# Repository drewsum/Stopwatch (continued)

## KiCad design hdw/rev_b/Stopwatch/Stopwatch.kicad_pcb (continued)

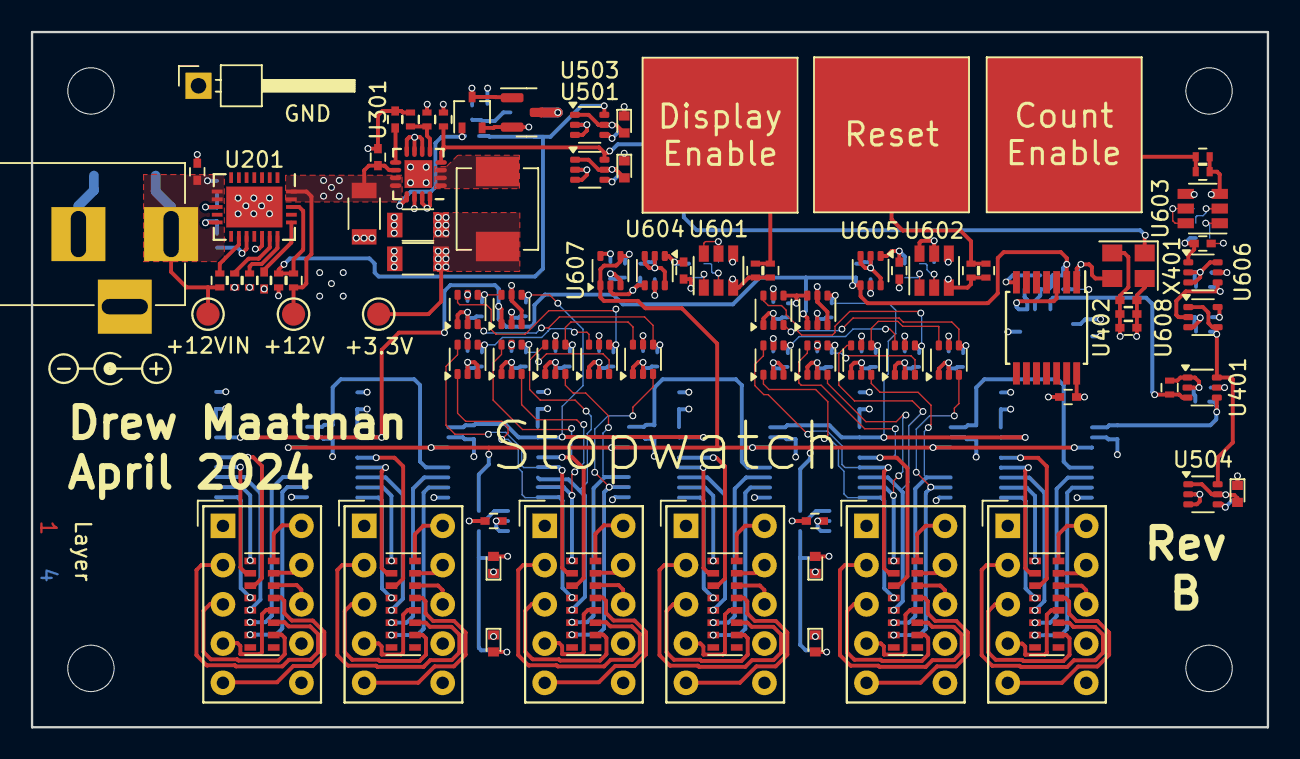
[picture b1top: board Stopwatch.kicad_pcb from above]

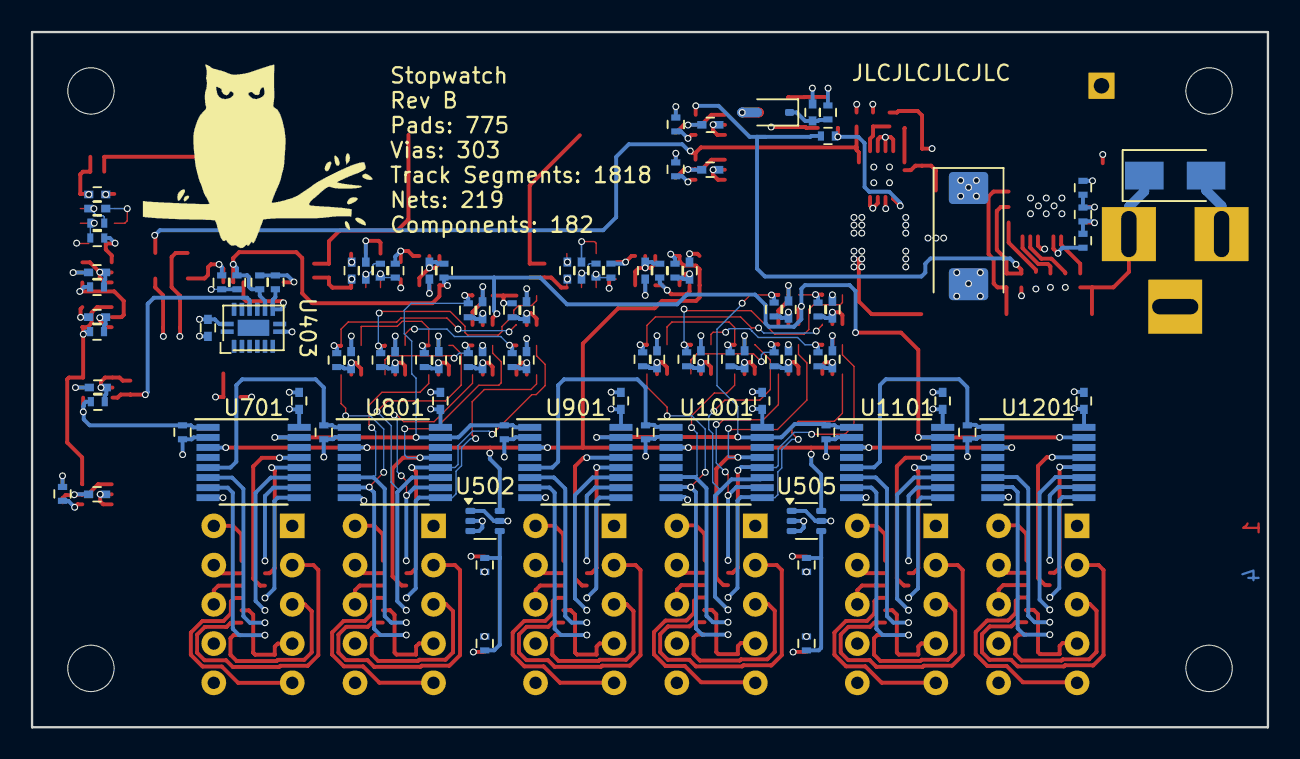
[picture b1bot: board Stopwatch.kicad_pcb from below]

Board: 4 copper layers, 80.0 x 45.0 mm, 192 parts (97 on the bottom side), 156 nets.

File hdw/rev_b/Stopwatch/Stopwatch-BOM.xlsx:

Reference | Value | Datasheet | Footprint | Qty | DNP | Config | Digi-Key PN
C201,C303,C402,C601,C602,C603 | 10nF |  | Capacitors_SMD:C_0402 | 6 |  |  | 445-12201-1-ND
C202,C304,C401,C404,C405,C406,C501,C502,C503,C504,C505,C604,C605,C606,C610,C611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 | 0.1uF |  | Capacitors_SMD:C_0402 | 39 |  |  | 490-10697-1-ND
C203 | 100uF |  | Capacitor_Tantalum_SMD:CP_EIA-7343-43_Kemet-X | 1 |  |  | 718-1102-1-ND
C301,C305,C306 | 10uF |  | Capacitors_SMD:C_1206 | 3 |  |  | 1276-7031-1-ND
C302,C607,C608,C609 | 10uF |  | Capacitors_SMD:C_0402 | 4 |  |  | 490-GRM155R61A106ME11DCT-ND
C403 | 1nF |  | Capacitors_SMD:C_0402 | 1 |  |  | 445-7376-1-ND
D201 | 24V | ~ | Diodes_SMD:D_SMA | 1 | DNP | DNP | SMAJ24CALFCT-ND
D301 | BAT48JFILM | www.st.com/resource/en/datasheet/bat48.pdf | Diode_SMD:D_SOD-323 | 1 |  |  | 497-5711-1-ND
D501,D504,D505 | Green | ~ | LEDs:LED_0402 | 3 |  |  | 754-1101-1-ND
D502,D503,D506,D507 | Red | ~ | LEDs:LED_0402 | 4 |  |  | 754-1104-1-ND
H1501,H1502,H1503,H1504 | 3mm | ~ | MountingHole:MountingHole_3mm | 4
J201 | +12V IN | ~ | Connectors:BARREL_JACK | 1 |  |  | CP-202BH-ND
L301 | 2.2u |  | Inductors_SMD:L_Vishay_IHLP-2020 | 1 |  |  | 541-1236-1-ND
N201 | +12V 1A Power Supply | ~ |  | 1 |  |  | 993-1335-ND
Q301 | BSS214NW | https://www.infineon.com/dgdl/Infineon-BSS214NW-DS-v02_02-en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 | Package_TO_SOT_SMD:SOT-323_SC-70 | 1 |  |  | BSS214NWH6327XTSA1CT-ND
Q302 | ZXMS6004FFTA | https://www.diodes.com/assets/Datasheets/ZXMS6004FF.pdf | Package_TO_SOT_SMD:SOT-23 | 1 |  |  | ZXMS6004FFCT-ND
R201 | 51.1k |  | Resistors_SMD:R_0402 | 1 |  |  | RMCF0402FT51K1CT-ND
R202 | 1.15k |  | Resistors_SMD:R_0402 | 1 |  |  | RMCF0402FT1K15CT-ND
R203,R207 | 5.11k |  | Resistors_SMD:R_0402 | 2 |  |  | RMCF0402FT5K11CT-ND
R204,R205,R208,R302,R303,R401,R402,R403,R404,R405,R406,R607,R608,R609,R610,R611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 | 10k |  | Resistors_SMD:R_0402 | 42 |  |  | RMCF0402FT10K0CT-ND
R206 | 13k |  | Resistors_SMD:R_0402 | 1 |  |  | RMCF0402FT13K0CT-ND
R301 | 10 |  | Resistors_SMD:R_0402 | 1 |  |  | RMCF0402FT10R0CT-ND
R304 | 562k |  | Resistors_SMD:R_0402 | 1 |  |  | RMCF0402FT562KCT-ND
R305 | 180k |  | Resistors_SMD:R_0402 | 1 |  |  | RMCF0402FT180KCT-ND
R501,R502,R503,R504,R505,R506,R507,R601,R602,R603,R604,R605,R606 | 1k |  | Resistors_SMD:R_0402 | 13 |  |  | RMCF0402FT1K00CT-ND
RN701,RN801,RN901,RN1001,RN1101,RN1201 | 1k |  | Resistor_SMD:R_Cat16-8 | 6 |  |  | CAT16-102J8LFCT-ND
SW601,SW602,SW603 | Cap_Touch |  | Custom Footprints Library:Capacitive_Touch_Pad | 3
TP201 | TP |  | Connector_PinHeader_2.54mm:PinHeader_1x01_P2.54mm_Horizontal | 1
TP202,TP203 | TP_Pad |  | Custom Footprints Library:Test_Point | 2
TP301 | TP |  | Custom Footprints Library:Test_Point | 1
U201 | TPS26600RHFT | http://www.ti.com/lit/ds/symlink/tps2660.pdf | Housings_DFN_QFN:QFN-24-1EP_4x5mm_Pitch0.5mm | 1 |  |  | 296-45478-1-ND
U301 | TPS62130A | http://www.ti.com/lit/ds/symlink/tps62130.pdf | Housings_DFN_QFN:QFN-16-1EP_3x3mm_Pitch0.5mm | 1 |  |  | 296-39446-1-ND
U401,U501,U502,U503,U504,U505,U604,U605,U606,U1301,U1302,U1303,U1304,U1305,U130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 | 74LVC1G97 | http://www.ti.com/lit/ds/symlink/sn74lvc1g97.pdf | Package_TO_SOT_SMD:SOT-363_SC-70-6 | 23 |  |  | 296-15582-1-ND
U402 | CD4024 | http://www.ti.com/lit/ds/symlink/cd4020b.pdf | Housings_SSOP:TSSOP-14_4.4x5mm_Pitch0.65mm | 1 |  |  | 296-49578-ND
U403 | CD4040 | http://www.intersil.com/content/dam/Intersil/documents/cd40/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 | Custom Footprints Library:DHVQFN16-1ep_3p5x2p5mm | 1 |  |  | 1727-7992-1-ND
U601,U602,U603 | AT42QT1010-TSHR | http://ww1.microchip.com/downloads/en/DeviceDoc/Atmel-9541-A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 | TO_SOT_Packages_SMD:SOT-23-6 | 3 |  |  | AT42QT1010-TSHRCT-ND
U607,U608 | 74LVC1G80 | http://www.ti.com/lit/sg/scyt129e/scyt129e.pdf | Package_TO_SOT_SMD:SOT-353_SC-70-5 | 2 |  |  | 296-41824-1-ND
U701,U801,U901,U1001,U1101,U1201 | 4026 |  | Housings_SSOP:TSSOP-16_4.4x5mm_Pitch0.65mm | 6 |  |  | 296-32878-5-ND
U702,U802,U902,U1002,U1102,U1202 | HDSP-7503 | https://docs.broadcom.com/docs/AV02-2553EN | Display_7Segment:HDSP-A151 | 6 |  |  | 516-1203-5-ND
X401 | ECS-327KE |  | Oscillator:Oscillator_SMD_Abracon_ASE-4Pin_3.2x2.5mm | 1 |  |  | XC1751CT-ND

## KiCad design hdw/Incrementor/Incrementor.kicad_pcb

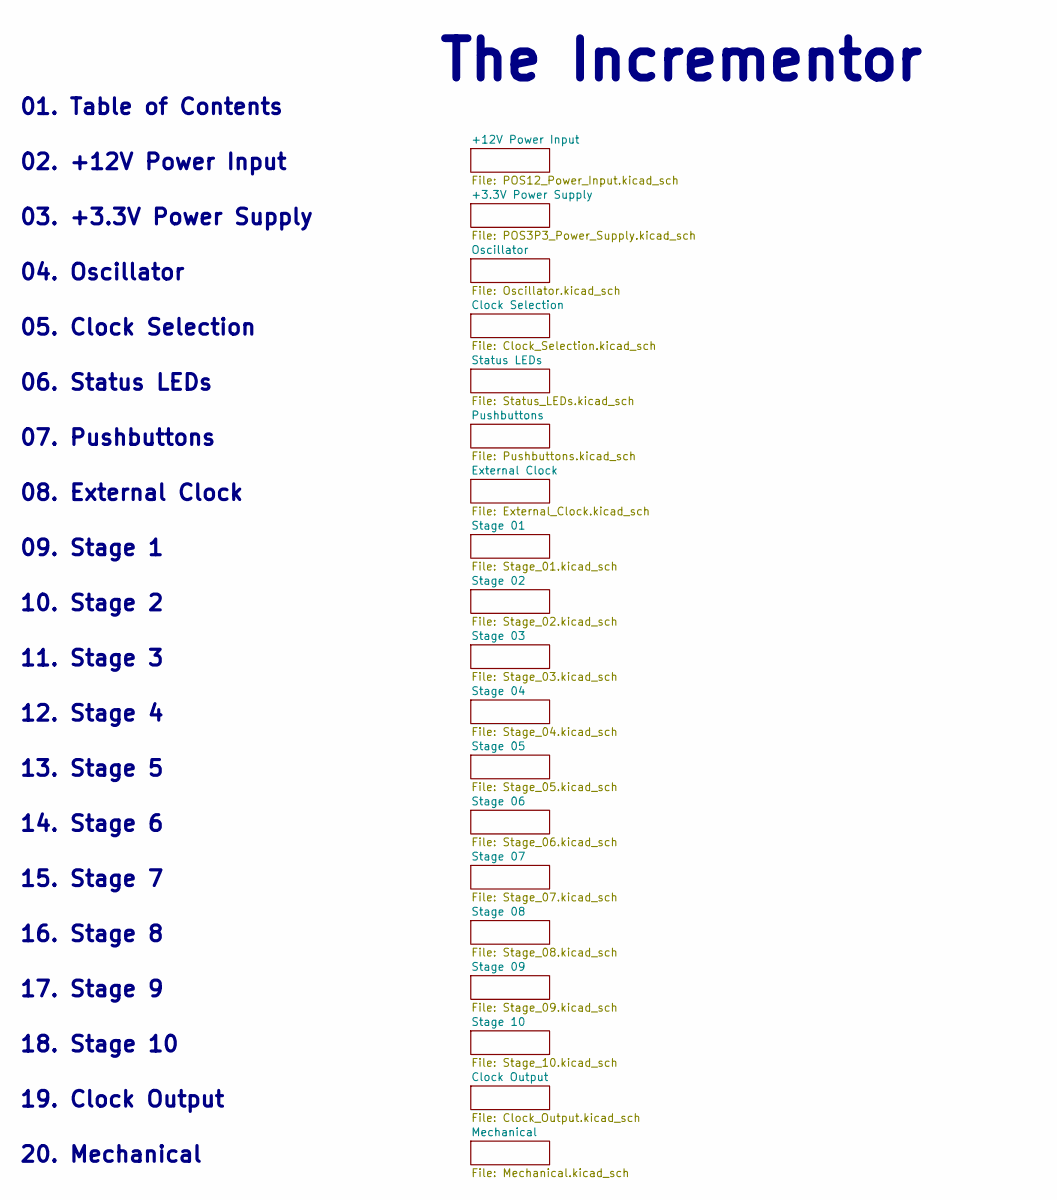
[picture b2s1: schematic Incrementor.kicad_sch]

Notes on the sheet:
14. Stage 6
18. Stage 10
17. Stage 9
11. Stage 3
19. Clock Output
06. Status LEDs
08. External Clock
20. Mechanical
12. Stage 4
16. Stage 8
15. Stage 7
The Incrementor
03. +3.3V Power Supply
01. Table of Contents
05. Clock Selection
10. Stage 2
07. Pushbuttons
02. +12V Power Input
09. Stage 1
13. Stage 5
04. Oscillator

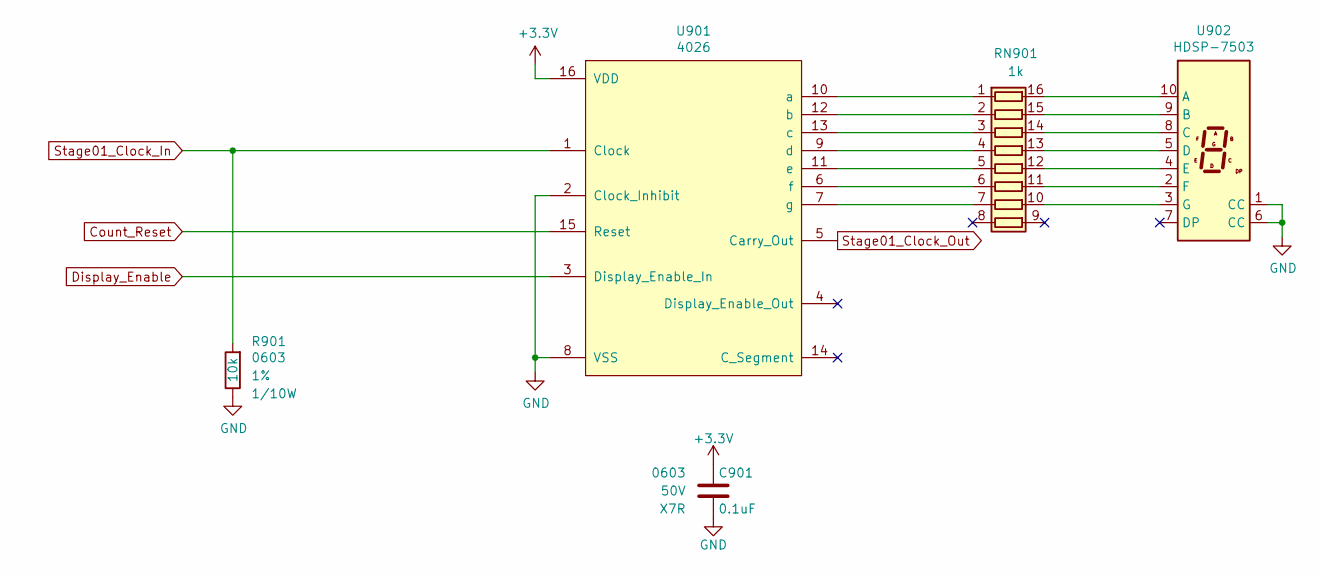
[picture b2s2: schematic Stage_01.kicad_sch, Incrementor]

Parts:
C901: 0.1uF; C_0603; Voltage 50V; Digi-Key PN 311-1344-1-ND
R901: 10k; R_0603; Tolerance 1%; Digi-Key PN RMCF0603FT10K0CT-ND
RN901: 1k; R_Cat16-8; Digi-Key PN CAT16-102J8LFCT-ND
U901: 4026; TSSOP-16_4.4x5mm_Pitch0.65mm; Digi-Key PN 296-32878-5-ND
U902: HDSP-7503; HDSP-A151; Digi-Key PN 516-1203-5-ND

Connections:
+3V3: C901.1, U901.16 (VDD); also elsewhere on the board
Count_Reset: U901.15 (Reset); also elsewhere on the board
Display_Enable: U901.3 (Display_Enable_In); also elsewhere on the board
GND: C901.2, R901.2, U901.2 (Clock_Inhibit), U901.8 (VSS), U902.1 (CC), U902.6 (CC); also elsewhere on the board
unnamed: RN901.1 (R1.1), U901.10 (a)
unnamed: RN901.2 (R2.1), U901.12 (b)
unnamed: RN901.3 (R3.1), U901.13 (c)
unnamed: RN901.4 (R4.1), U901.9 (d)
unnamed: RN901.5 (R5.1), U901.11 (e)
unnamed: RN901.6 (R6.1), U901.6 (f)
unnamed: RN901.7 (R7.1), U901.7 (g)
unnamed: RN901.10 (R7.2), U902.3 (G)
unnamed: RN901.11 (R6.2), U902.2 (F)
unnamed: RN901.12 (R5.2), U902.4 (E)
unnamed: RN901.13 (R4.2), U902.5 (D)
unnamed: RN901.14 (R3.2), U902.8 (C)
unnamed: RN901.15 (R2.2), U902.9 (B)
unnamed: RN901.16 (R1.2), U902.10 (A)
Stage01_Clock_In: R901.1, U901.1 (Clock); also elsewhere on the board
Stage01_Clock_Out: U901.5 (Carry_Out); also elsewhere on the board

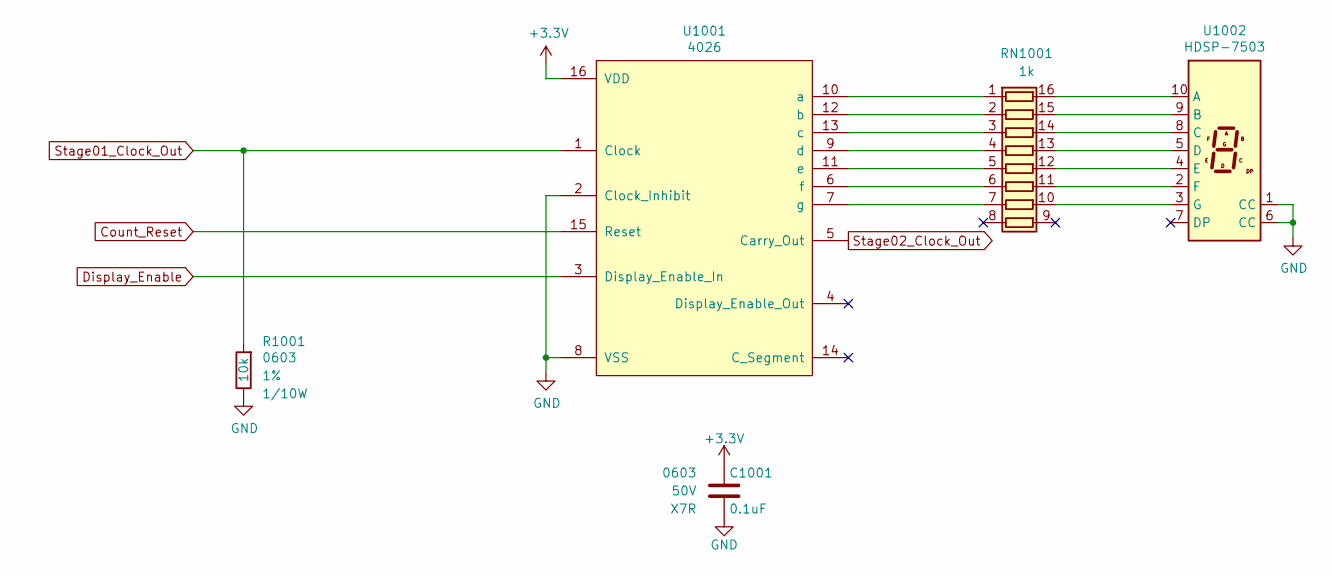
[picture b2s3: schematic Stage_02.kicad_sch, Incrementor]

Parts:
C1001: 0.1uF; C_0603; Voltage 50V; Digi-Key PN 311-1344-1-ND
R1001: 10k; R_0603; Tolerance 1%; Digi-Key PN RMCF0603FT10K0CT-ND
RN1001: 1k; R_Cat16-8; Digi-Key PN CAT16-102J8LFCT-ND
U1001: 4026; TSSOP-16_4.4x5mm_Pitch0.65mm; Digi-Key PN 296-32878-5-ND
U1002: HDSP-7503; HDSP-A151; Digi-Key PN 516-1203-5-ND

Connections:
+3V3: C1001.1, U1001.16 (VDD); also elsewhere on the board
Count_Reset: U1001.15 (Reset); also elsewhere on the board
Display_Enable: U1001.3 (Display_Enable_In); also elsewhere on the board
GND: C1001.2, R1001.2, U1001.2 (Clock_Inhibit), U1001.8 (VSS), U1002.1 (CC), U1002.6 (CC); also elsewhere on the board
unnamed: RN1001.1 (R1.1), U1001.10 (a)
unnamed: RN1001.2 (R2.1), U1001.12 (b)
unnamed: RN1001.3 (R3.1), U1001.13 (c)
unnamed: RN1001.4 (R4.1), U1001.9 (d)
unnamed: RN1001.5 (R5.1), U1001.11 (e)
unnamed: RN1001.6 (R6.1), U1001.6 (f)
unnamed: RN1001.7 (R7.1), U1001.7 (g)
unnamed: RN1001.10 (R7.2), U1002.3 (G)
unnamed: RN1001.11 (R6.2), U1002.2 (F)
unnamed: RN1001.12 (R5.2), U1002.4 (E)
unnamed: RN1001.13 (R4.2), U1002.5 (D)
unnamed: RN1001.14 (R3.2), U1002.8 (C)
unnamed: RN1001.15 (R2.2), U1002.9 (B)
unnamed: RN1001.16 (R1.2), U1002.10 (A)
Stage01_Clock_Out: R1001.1, U1001.1 (Clock); also elsewhere on the board
Stage02_Clock_Out: U1001.5 (Carry_Out); also elsewhere on the board

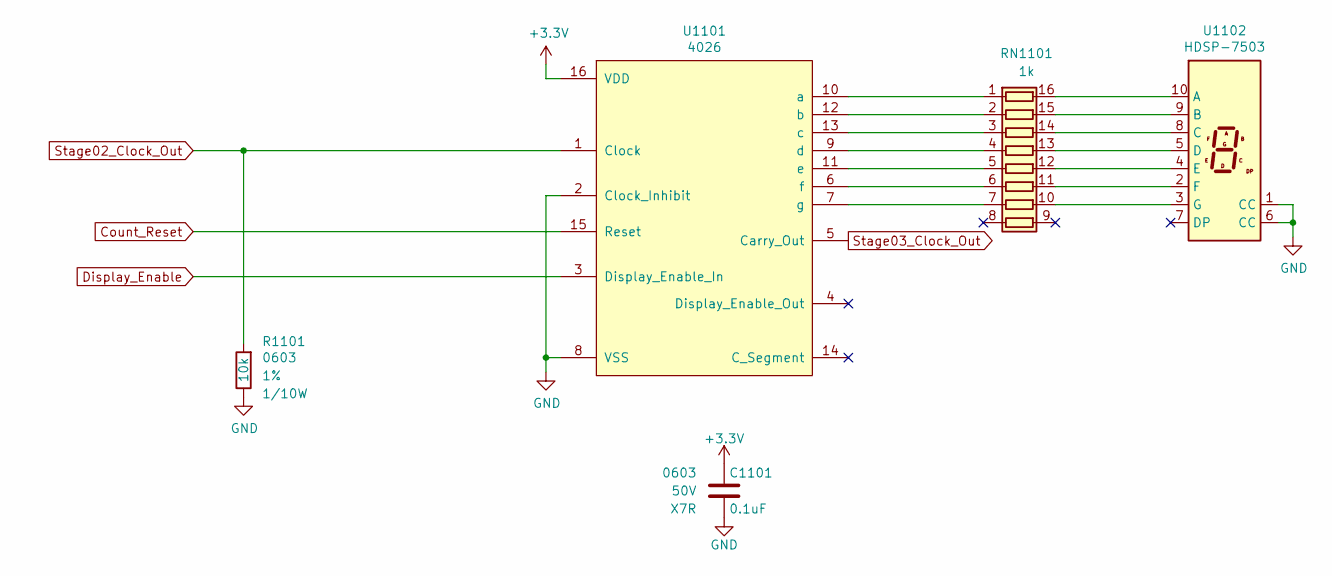
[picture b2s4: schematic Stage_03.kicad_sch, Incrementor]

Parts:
C1101: 0.1uF; C_0603; Voltage 50V; Digi-Key PN 311-1344-1-ND
R1101: 10k; R_0603; Tolerance 1%; Digi-Key PN RMCF0603FT10K0CT-ND
RN1101: 1k; R_Cat16-8; Digi-Key PN CAT16-102J8LFCT-ND
U1101: 4026; TSSOP-16_4.4x5mm_Pitch0.65mm; Digi-Key PN 296-32878-5-ND
U1102: HDSP-7503; HDSP-A151; Digi-Key PN 516-1203-5-ND

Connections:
+3V3: C1101.1, U1101.16 (VDD); also elsewhere on the board
Count_Reset: U1101.15 (Reset); also elsewhere on the board
Display_Enable: U1101.3 (Display_Enable_In); also elsewhere on the board
GND: C1101.2, R1101.2, U1101.2 (Clock_Inhibit), U1101.8 (VSS), U1102.1 (CC), U1102.6 (CC); also elsewhere on the board
unnamed: RN1101.1 (R1.1), U1101.10 (a)
unnamed: RN1101.2 (R2.1), U1101.12 (b)
unnamed: RN1101.3 (R3.1), U1101.13 (c)
unnamed: RN1101.4 (R4.1), U1101.9 (d)
unnamed: RN1101.5 (R5.1), U1101.11 (e)
unnamed: RN1101.6 (R6.1), U1101.6 (f)
unnamed: RN1101.7 (R7.1), U1101.7 (g)
unnamed: RN1101.10 (R7.2), U1102.3 (G)
unnamed: RN1101.11 (R6.2), U1102.2 (F)
unnamed: RN1101.12 (R5.2), U1102.4 (E)
unnamed: RN1101.13 (R4.2), U1102.5 (D)
unnamed: RN1101.14 (R3.2), U1102.8 (C)
unnamed: RN1101.15 (R2.2), U1102.9 (B)
unnamed: RN1101.16 (R1.2), U1102.10 (A)
Stage02_Clock_Out: R1101.1, U1101.1 (Clock); also elsewhere on the board
Stage03_Clock_Out: U1101.5 (Carry_Out); also elsewhere on the board

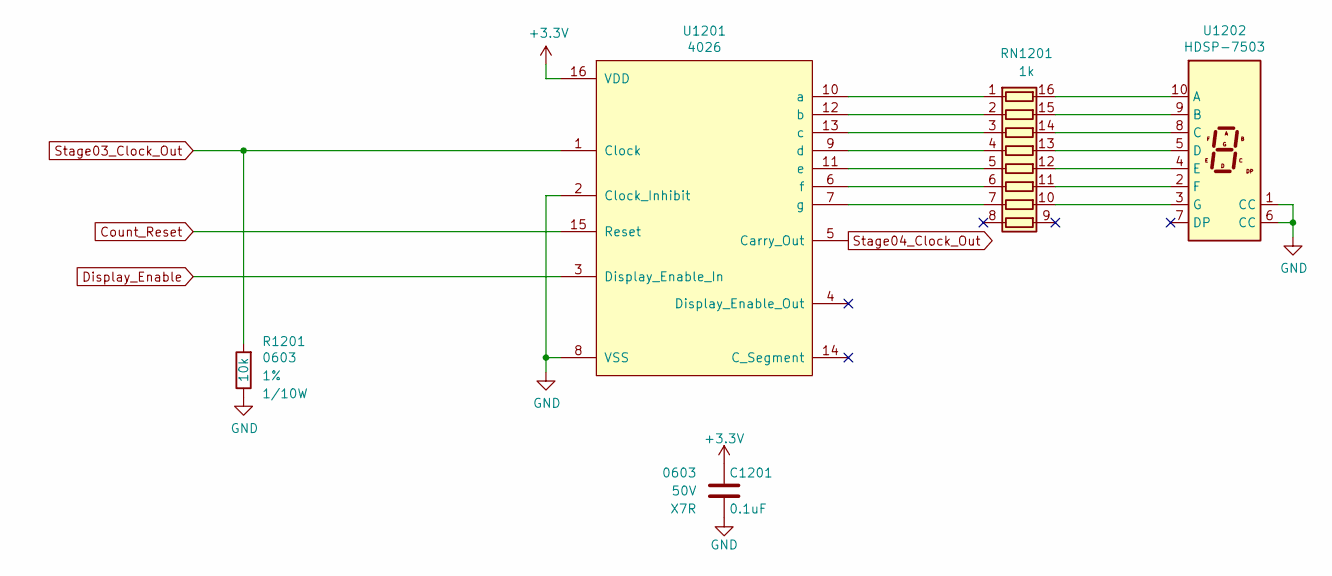
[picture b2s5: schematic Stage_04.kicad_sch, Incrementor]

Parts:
C1201: 0.1uF; C_0603; Voltage 50V; Digi-Key PN 311-1344-1-ND
R1201: 10k; R_0603; Tolerance 1%; Digi-Key PN RMCF0603FT10K0CT-ND
RN1201: 1k; R_Cat16-8; Digi-Key PN CAT16-102J8LFCT-ND
U1201: 4026; TSSOP-16_4.4x5mm_Pitch0.65mm; Digi-Key PN 296-32878-5-ND
U1202: HDSP-7503; HDSP-A151; Digi-Key PN 516-1203-5-ND

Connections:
+3V3: C1201.1, U1201.16 (VDD); also elsewhere on the board
Count_Reset: U1201.15 (Reset); also elsewhere on the board
Display_Enable: U1201.3 (Display_Enable_In); also elsewhere on the board
GND: C1201.2, R1201.2, U1201.2 (Clock_Inhibit), U1201.8 (VSS), U1202.1 (CC), U1202.6 (CC); also elsewhere on the board
unnamed: RN1201.1 (R1.1), U1201.10 (a)
unnamed: RN1201.2 (R2.1), U1201.12 (b)
unnamed: RN1201.3 (R3.1), U1201.13 (c)
unnamed: RN1201.4 (R4.1), U1201.9 (d)
unnamed: RN1201.5 (R5.1), U1201.11 (e)
unnamed: RN1201.6 (R6.1), U1201.6 (f)
unnamed: RN1201.7 (R7.1), U1201.7 (g)
unnamed: RN1201.10 (R7.2), U1202.3 (G)
unnamed: RN1201.11 (R6.2), U1202.2 (F)
unnamed: RN1201.12 (R5.2), U1202.4 (E)
unnamed: RN1201.13 (R4.2), U1202.5 (D)
unnamed: RN1201.14 (R3.2), U1202.8 (C)
unnamed: RN1201.15 (R2.2), U1202.9 (B)
unnamed: RN1201.16 (R1.2), U1202.10 (A)
Stage03_Clock_Out: R1201.1, U1201.1 (Clock); also elsewhere on the board
Stage04_Clock_Out: U1201.5 (Carry_Out); also elsewhere on the board

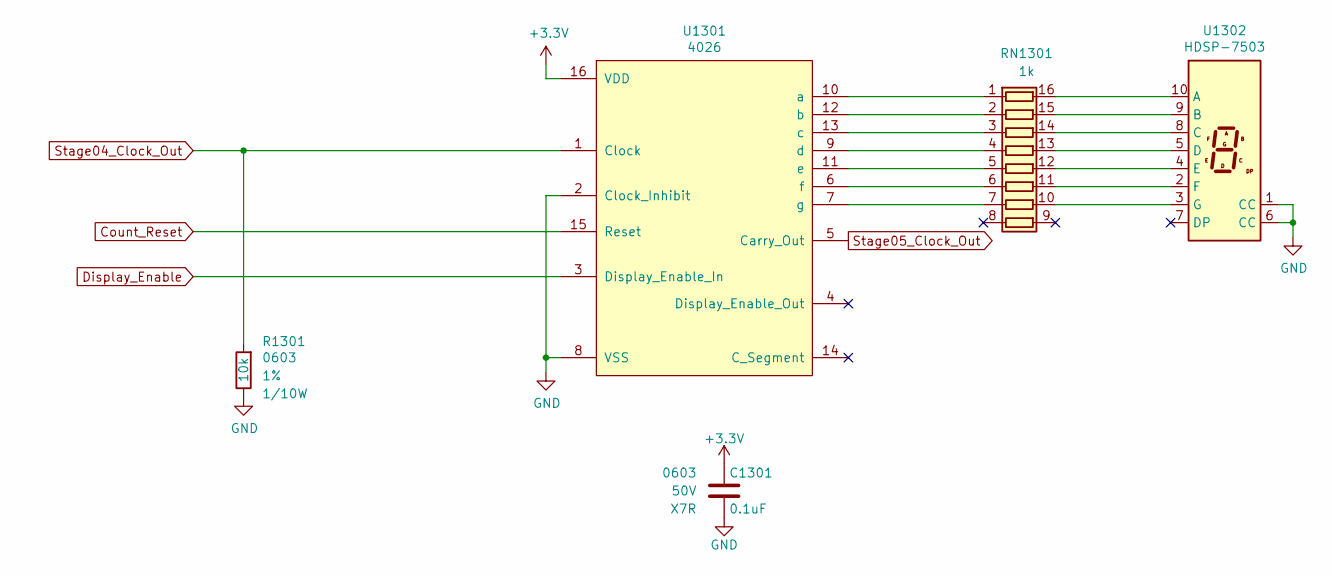
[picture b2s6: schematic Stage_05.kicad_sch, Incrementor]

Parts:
C1301: 0.1uF; C_0603; Voltage 50V; Digi-Key PN 311-1344-1-ND
R1301: 10k; R_0603; Tolerance 1%; Digi-Key PN RMCF0603FT10K0CT-ND
RN1301: 1k; R_Cat16-8; Digi-Key PN CAT16-102J8LFCT-ND
U1301: 4026; TSSOP-16_4.4x5mm_Pitch0.65mm; Digi-Key PN 296-32878-5-ND
U1302: HDSP-7503; HDSP-A151; Digi-Key PN 516-1203-5-ND

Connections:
+3V3: C1301.1, U1301.16 (VDD); also elsewhere on the board
Count_Reset: U1301.15 (Reset); also elsewhere on the board
Display_Enable: U1301.3 (Display_Enable_In); also elsewhere on the board
GND: C1301.2, R1301.2, U1301.2 (Clock_Inhibit), U1301.8 (VSS), U1302.1 (CC), U1302.6 (CC); also elsewhere on the board
unnamed: RN1301.1 (R1.1), U1301.10 (a)
unnamed: RN1301.2 (R2.1), U1301.12 (b)
unnamed: RN1301.3 (R3.1), U1301.13 (c)
unnamed: RN1301.4 (R4.1), U1301.9 (d)
unnamed: RN1301.5 (R5.1), U1301.11 (e)
unnamed: RN1301.6 (R6.1), U1301.6 (f)
unnamed: RN1301.7 (R7.1), U1301.7 (g)
unnamed: RN1301.10 (R7.2), U1302.3 (G)
unnamed: RN1301.11 (R6.2), U1302.2 (F)
unnamed: RN1301.12 (R5.2), U1302.4 (E)
unnamed: RN1301.13 (R4.2), U1302.5 (D)
unnamed: RN1301.14 (R3.2), U1302.8 (C)
unnamed: RN1301.15 (R2.2), U1302.9 (B)
unnamed: RN1301.16 (R1.2), U1302.10 (A)
Stage04_Clock_Out: R1301.1, U1301.1 (Clock); also elsewhere on the board
Stage05_Clock_Out: U1301.5 (Carry_Out); also elsewhere on the board

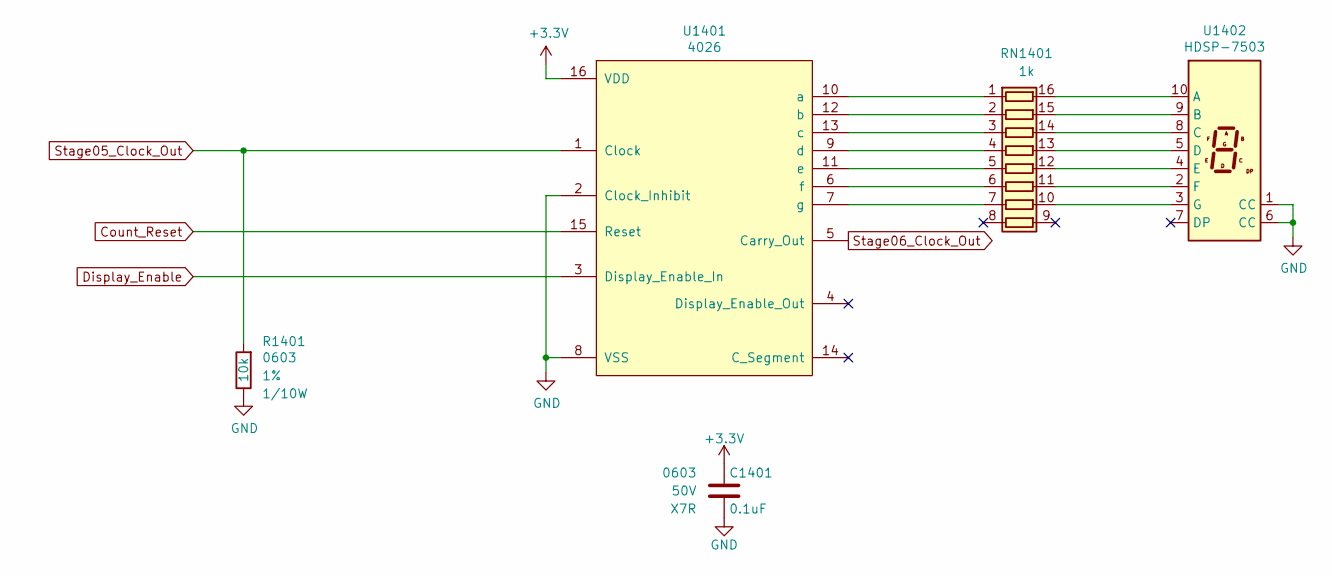
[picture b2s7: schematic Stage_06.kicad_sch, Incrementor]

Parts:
C1401: 0.1uF; C_0603; Voltage 50V; Digi-Key PN 311-1344-1-ND
R1401: 10k; R_0603; Tolerance 1%; Digi-Key PN RMCF0603FT10K0CT-ND
RN1401: 1k; R_Cat16-8; Digi-Key PN CAT16-102J8LFCT-ND
U1401: 4026; TSSOP-16_4.4x5mm_Pitch0.65mm; Digi-Key PN 296-32878-5-ND
U1402: HDSP-7503; HDSP-A151; Digi-Key PN 516-1203-5-ND

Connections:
+3V3: C1401.1, U1401.16 (VDD); also elsewhere on the board
Count_Reset: U1401.15 (Reset); also elsewhere on the board
Display_Enable: U1401.3 (Display_Enable_In); also elsewhere on the board
GND: C1401.2, R1401.2, U1401.2 (Clock_Inhibit), U1401.8 (VSS), U1402.1 (CC), U1402.6 (CC); also elsewhere on the board
unnamed: RN1401.1 (R1.1), U1401.10 (a)
unnamed: RN1401.2 (R2.1), U1401.12 (b)
unnamed: RN1401.3 (R3.1), U1401.13 (c)
unnamed: RN1401.4 (R4.1), U1401.9 (d)
unnamed: RN1401.5 (R5.1), U1401.11 (e)
unnamed: RN1401.6 (R6.1), U1401.6 (f)
unnamed: RN1401.7 (R7.1), U1401.7 (g)
unnamed: RN1401.10 (R7.2), U1402.3 (G)
unnamed: RN1401.11 (R6.2), U1402.2 (F)
unnamed: RN1401.12 (R5.2), U1402.4 (E)
unnamed: RN1401.13 (R4.2), U1402.5 (D)
unnamed: RN1401.14 (R3.2), U1402.8 (C)
unnamed: RN1401.15 (R2.2), U1402.9 (B)
unnamed: RN1401.16 (R1.2), U1402.10 (A)
Stage05_Clock_Out: R1401.1, U1401.1 (Clock); also elsewhere on the board
Stage06_Clock_Out: U1401.5 (Carry_Out); also elsewhere on the board

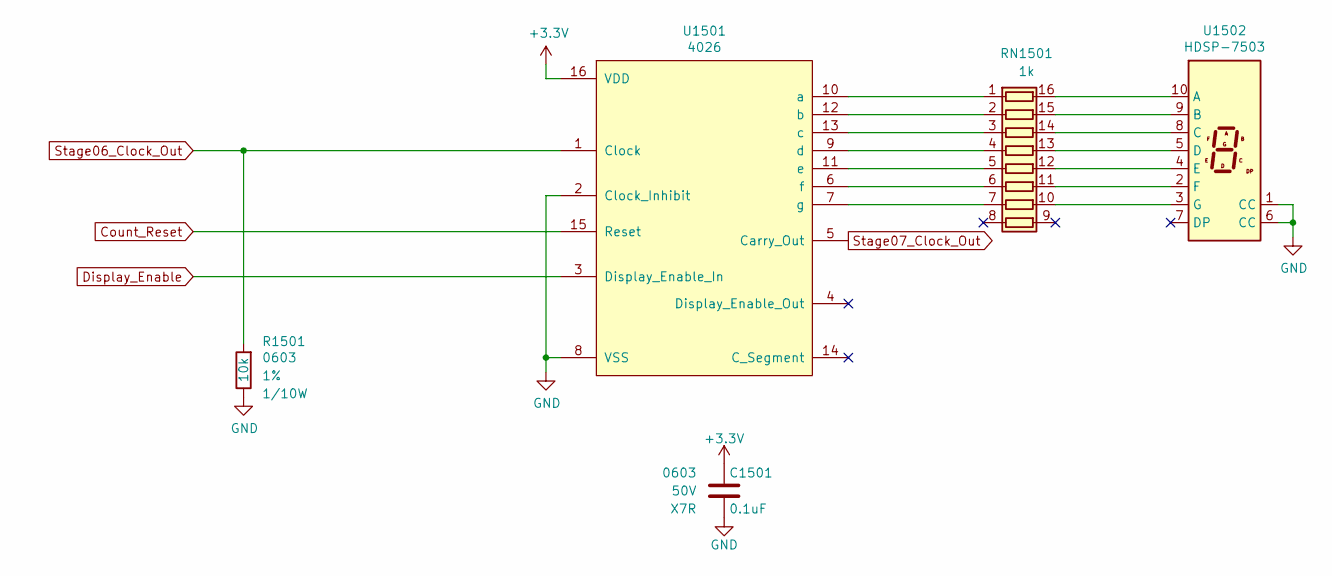
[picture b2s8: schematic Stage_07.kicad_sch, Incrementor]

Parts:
C1501: 0.1uF; C_0603; Voltage 50V; Digi-Key PN 311-1344-1-ND
R1501: 10k; R_0603; Tolerance 1%; Digi-Key PN RMCF0603FT10K0CT-ND
RN1501: 1k; R_Cat16-8; Digi-Key PN CAT16-102J8LFCT-ND
U1501: 4026; TSSOP-16_4.4x5mm_Pitch0.65mm; Digi-Key PN 296-32878-5-ND
U1502: HDSP-7503; HDSP-A151; Digi-Key PN 516-1203-5-ND

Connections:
+3V3: C1501.1, U1501.16 (VDD); also elsewhere on the board
Count_Reset: U1501.15 (Reset); also elsewhere on the board
Display_Enable: U1501.3 (Display_Enable_In); also elsewhere on the board
GND: C1501.2, R1501.2, U1501.2 (Clock_Inhibit), U1501.8 (VSS), U1502.1 (CC), U1502.6 (CC); also elsewhere on the board
unnamed: RN1501.1 (R1.1), U1501.10 (a)
unnamed: RN1501.2 (R2.1), U1501.12 (b)
unnamed: RN1501.3 (R3.1), U1501.13 (c)
unnamed: RN1501.4 (R4.1), U1501.9 (d)
unnamed: RN1501.5 (R5.1), U1501.11 (e)
unnamed: RN1501.6 (R6.1), U1501.6 (f)
unnamed: RN1501.7 (R7.1), U1501.7 (g)
unnamed: RN1501.10 (R7.2), U1502.3 (G)
unnamed: RN1501.11 (R6.2), U1502.2 (F)
unnamed: RN1501.12 (R5.2), U1502.4 (E)
unnamed: RN1501.13 (R4.2), U1502.5 (D)
unnamed: RN1501.14 (R3.2), U1502.8 (C)
unnamed: RN1501.15 (R2.2), U1502.9 (B)
unnamed: RN1501.16 (R1.2), U1502.10 (A)
Stage06_Clock_Out: R1501.1, U1501.1 (Clock); also elsewhere on the board
Stage07_Clock_Out: U1501.5 (Carry_Out); also elsewhere on the board

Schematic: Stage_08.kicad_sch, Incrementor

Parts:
C1601: 0.1uF; C_0603; Voltage 50V; Digi-Key PN 311-1344-1-ND
R1601: 10k; R_0603; Tolerance 1%; Digi-Key PN RMCF0603FT10K0CT-ND
RN1601: 1k; R_Cat16-8; Digi-Key PN CAT16-102J8LFCT-ND
U1601: 4026; TSSOP-16_4.4x5mm_Pitch0.65mm; Digi-Key PN 296-32878-5-ND
U1602: HDSP-7503; HDSP-A151; Digi-Key PN 516-1203-5-ND

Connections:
+3V3: C1601.1, U1601.16 (VDD); also elsewhere on the board
Count_Reset: U1601.15 (Reset); also elsewhere on the board
Display_Enable: U1601.3 (Display_Enable_In); also elsewhere on the board
GND: C1601.2, R1601.2, U1601.2 (Clock_Inhibit), U1601.8 (VSS), U1602.1 (CC), U1602.6 (CC); also elsewhere on the board
unnamed: RN1601.1 (R1.1), U1601.10 (a)
unnamed: RN1601.2 (R2.1), U1601.12 (b)
unnamed: RN1601.3 (R3.1), U1601.13 (c)
unnamed: RN1601.4 (R4.1), U1601.9 (d)
unnamed: RN1601.5 (R5.1), U1601.11 (e)
unnamed: RN1601.6 (R6.1), U1601.6 (f)
unnamed: RN1601.7 (R7.1), U1601.7 (g)
unnamed: RN1601.10 (R7.2), U1602.3 (G)
unnamed: RN1601.11 (R6.2), U1602.2 (F)
unnamed: RN1601.12 (R5.2), U1602.4 (E)
unnamed: RN1601.13 (R4.2), U1602.5 (D)
unnamed: RN1601.14 (R3.2), U1602.8 (C)
unnamed: RN1601.15 (R2.2), U1602.9 (B)
unnamed: RN1601.16 (R1.2), U1602.10 (A)
Stage07_Clock_Out: R1601.1, U1601.1 (Clock); also elsewhere on the board
Stage08_Clock_Out: U1601.5 (Carry_Out); also elsewhere on the board

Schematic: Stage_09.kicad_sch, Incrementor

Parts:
C1701: 0.1uF; C_0603; Voltage 50V; Digi-Key PN 311-1344-1-ND
R1701: 10k; R_0603; Tolerance 1%; Digi-Key PN RMCF0603FT10K0CT-ND
RN1701: 1k; R_Cat16-8; Digi-Key PN CAT16-102J8LFCT-ND
U1701: 4026; TSSOP-16_4.4x5mm_Pitch0.65mm; Digi-Key PN 296-32878-5-ND
U1702: HDSP-7503; HDSP-A151; Digi-Key PN 516-1203-5-ND

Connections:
+3V3: C1701.1, U1701.16 (VDD); also elsewhere on the board
Count_Reset: U1701.15 (Reset); also elsewhere on the board
Display_Enable: U1701.3 (Display_Enable_In); also elsewhere on the board
GND: C1701.2, R1701.2, U1701.2 (Clock_Inhibit), U1701.8 (VSS), U1702.1 (CC), U1702.6 (CC); also elsewhere on the board
unnamed: RN1701.1 (R1.1), U1701.10 (a)
unnamed: RN1701.2 (R2.1), U1701.12 (b)
unnamed: RN1701.3 (R3.1), U1701.13 (c)
unnamed: RN1701.4 (R4.1), U1701.9 (d)
unnamed: RN1701.5 (R5.1), U1701.11 (e)
unnamed: RN1701.6 (R6.1), U1701.6 (f)
unnamed: RN1701.7 (R7.1), U1701.7 (g)
unnamed: RN1701.10 (R7.2), U1702.3 (G)
unnamed: RN1701.11 (R6.2), U1702.2 (F)
unnamed: RN1701.12 (R5.2), U1702.4 (E)
unnamed: RN1701.13 (R4.2), U1702.5 (D)
unnamed: RN1701.14 (R3.2), U1702.8 (C)
unnamed: RN1701.15 (R2.2), U1702.9 (B)
unnamed: RN1701.16 (R1.2), U1702.10 (A)
Stage08_Clock_Out: R1701.1, U1701.1 (Clock); also elsewhere on the board
Stage09_Clock_Out: U1701.5 (Carry_Out); also elsewhere on the board

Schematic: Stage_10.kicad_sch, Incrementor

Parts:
C1801: 0.1uF; C_0603; Voltage 50V; Digi-Key PN 311-1344-1-ND
R1801: 10k; R_0603; Tolerance 1%; Digi-Key PN RMCF0603FT10K0CT-ND
RN1801: 1k; R_Cat16-8; Digi-Key PN CAT16-102J8LFCT-ND
U1801: 4026; TSSOP-16_4.4x5mm_Pitch0.65mm; Digi-Key PN 296-32878-5-ND
U1802: HDSP-7503; HDSP-A151; Digi-Key PN 516-1203-5-ND

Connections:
+3V3: C1801.1, U1801.16 (VDD); also elsewhere on the board
Count_Reset: U1801.15 (Reset); also elsewhere on the board
Display_Enable: U1801.3 (Display_Enable_In); also elsewhere on the board
GND: C1801.2, R1801.2, U1801.2 (Clock_Inhibit), U1801.8 (VSS), U1802.1 (CC), U1802.6 (CC); also elsewhere on the board
unnamed: RN1801.1 (R1.1), U1801.10 (a)
unnamed: RN1801.2 (R2.1), U1801.12 (b)
unnamed: RN1801.3 (R3.1), U1801.13 (c)
unnamed: RN1801.4 (R4.1), U1801.9 (d)
unnamed: RN1801.5 (R5.1), U1801.11 (e)
unnamed: RN1801.6 (R6.1), U1801.6 (f)
unnamed: RN1801.7 (R7.1), U1801.7 (g)
unnamed: RN1801.10 (R7.2), U1802.3 (G)
unnamed: RN1801.11 (R6.2), U1802.2 (F)
unnamed: RN1801.12 (R5.2), U1802.4 (E)
unnamed: RN1801.13 (R4.2), U1802.5 (D)
unnamed: RN1801.14 (R3.2), U1802.8 (C)
unnamed: RN1801.15 (R2.2), U1802.9 (B)
unnamed: RN1801.16 (R1.2), U1802.10 (A)
Stage09_Clock_Out: R1801.1, U1801.1 (Clock); also elsewhere on the board
Stage10_Clock_Out: U1801.5 (Carry_Out); also elsewhere on the board

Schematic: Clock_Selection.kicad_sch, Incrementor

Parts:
C501, C502, C503, C504, C505, C506, C507, C508: 0.1uF; C_0603; Voltage 50V; Digi-Key PN 311-1344-1-ND
R501, R502, R503, R504, R505, R506, R507, R508, R509, R510, R511, R512, R513, R514, R515: 10k; R_0603; Tolerance 1%; Digi-Key PN RMCF0603FT10K0CT-ND
U501, U502, U503, U504, U505, U506: 74LVC1G08; Fairchild_MicroPak2-6_1.0x1.0mm_P0.35mm; Digi-Key PN 296-28375-1-ND
U507: 4072; TSSOP-14_4.4x5mm_Pitch0.65mm; Digi-Key PN 296-32907-5-ND
U508: 4017; DHVQFN16-1ep_3p5x2p5mm; Digi-Key PN 1727-7943-1-ND

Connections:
1Hz_Clock: R505.1, U505.1; also elsewhere on the board
1Hz_Clock_Select: R511.1, U505.2, U508.4 (Q2); also elsewhere on the board
4Hz_Clock: R504.1, U504.1; also elsewhere on the board
4Hz_Clock_Select: R510.1, U504.2, U508.7 (Q3); also elsewhere on the board
16Hz_Clock: R503.1, U503.1; also elsewhere on the board
16Hz_Clock_Select: R509.1, U503.2, U508.10 (Q4); also elsewhere on the board
256Hz_Clock: R502.1, U502.1; also elsewhere on the board
256Hz_Clock_Select: R508.1, U502.2, U508.1 (Q5); also elsewhere on the board
32768Hz_Clock: R501.1, U501.1; also elsewhere on the board
32768Hz_Clock_Select: R507.1, U501.2, U508.5 (Q6); also elsewhere on the board
+3V3: C501.1, C502.1, C503.1, C504.1, C505.1, C506.1, C507.1, C508.1, U501.6 (VCC), U502.6 (VCC), U503.6 (VCC), U504.6 (VCC), U505.6 (VCC), U506.6 (VCC), U507.14 (VDD), U508.16 (VDD); also elsewhere on the board
External_Clock: R506.1, U506.1; also elsewhere on the board
External_Clock_Select: R512.1, U506.2, U508.2 (Q1); also elsewhere on the board
GND: C501.2, C502.2, C503.2, C504.2, C505.2, C506.2, C507.2, C508.2, R501.2, R502.2, R503.2, R504.2, R505.2, R506.2, R507.2, R508.2, R509.2, R510.2, R511.2, R512.2, R513.2, R514.2, R515.2, U501.3 (GND), U502.3 (GND), U503.3 (GND), U504.3 (GND), U505.3 (GND), U506.3 (GND), U507.7 (VSS), U507.12, U508.8 (VSS), U508.17; also elsewhere on the board
unnamed: R514.1, U508.13 (CKEN)
unnamed: R515.1, U508.6 (Q7), U508.15 (Reset)
unnamed: U501.4, U507.2
unnamed: U502.4, U507.3
unnamed: U503.4, U507.4
unnamed: U504.4, U507.5
unnamed: U505.4, U507.10
unnamed: U506.4, U507.11
unnamed: U507.1, U507.9
Source_Select: R513.1, U508.14 (CLK); also elsewhere on the board
Stage01_Clock_In: U507.13; also elsewhere on the board
Suspend: U508.3 (Q0); also elsewhere on the board

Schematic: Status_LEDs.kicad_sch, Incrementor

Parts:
C601, C602, C603, C604, C605, C606, C607, C608, C609: 0.1uF; C_0603; Voltage 50V; Digi-Key PN 311-1344-1-ND
D601: Red; LED_0603; Digi-Key PN 160-1447-1-ND
D602, D603, D604, D605, D606, D607, D608, D609: Green; LED_0603; Digi-Key PN 160-1446-1-ND
R601, R602, R606, R607, R608, R612, R613: 10k; R_0603; Tolerance 1%; Digi-Key PN RMCF0603FT10K0CT-ND
R603, R604, R605, R609, R610, R611, R614, R615, R616: 1k; R_0603; Tolerance 1%; Digi-Key PN RHM1.0KDCT-ND
U601, U602, U603, U604, U605, U606, U607, U608, U609: 74LVC1G06; SOT-353_SC-70-5; Digi-Key PN 296-8484-1-ND

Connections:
1Hz_Clock_Select: R612.1, U607.2; also elsewhere on the board
4Hz_Clock_Select: R608.1, U606.2; also elsewhere on the board
16Hz_Clock_Select: R602.1, U602.2; also elsewhere on the board
256Hz_Clock_Select: R607.1, U605.2; also elsewhere on the board
32768Hz_Clock_Select: R613.1, U608.2; also elsewhere on the board
+3V3: C601.1, C602.1, C603.1, C604.1, C605.1, C606.1, C607.1, C608.1, C609.1, D601.2 (A), D602.2 (A), D603.2 (A), D604.2 (A), D605.2 (A), D606.2 (A), D607.2 (A), D608.2 (A), D609.2 (A), U601.5 (VCC), U602.5 (VCC), U603.5 (VCC), U604.5 (VCC), U605.5 (VCC), U606.5 (VCC), U607.5 (VCC), U608.5 (VCC), U609.5 (VCC); also elsewhere on the board
External_Clock_Select: R606.1, U604.2; also elsewhere on the board
GND: C601.2, C602.2, C603.2, C604.2, C605.2, C606.2, C607.2, C608.2, C609.2, R601.2, R602.2, R606.2, R607.2, R608.2, R612.2, R613.2, U601.3 (GND), U602.3 (GND), U603.3 (GND), U604.3 (GND), U605.3 (GND), U606.3 (GND), U607.3 (GND), U608.3 (GND), U609.3 (GND); also elsewhere on the board
unnamed: D601.1 (K), R603.1
unnamed: D602.1 (K), R604.1
unnamed: D603.1 (K), R605.1
unnamed: D604.1 (K), R609.1
unnamed: D605.1 (K), R610.1
unnamed: D606.1 (K), R611.1
unnamed: D607.1 (K), R614.1
unnamed: D608.1 (K), R615.1
unnamed: D609.1 (K), R616.1
unnamed: R603.2, U601.4
unnamed: R604.2, U602.4
unnamed: R605.2, U603.4
unnamed: R609.2, U604.4
unnamed: R610.2, U605.4
unnamed: R611.2, U606.4
unnamed: R614.2, U607.4
unnamed: R615.2, U608.4
unnamed: R616.2, U609.4
POS3P3_PGOOD: U609.2; also elsewhere on the board
POS12_PGOOD: U603.2; also elsewhere on the board
Suspend: R601.1, U601.2; also elsewhere on the board
